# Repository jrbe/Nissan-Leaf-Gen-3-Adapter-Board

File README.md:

# Nissan-Leaf-Gen-3-Adapter-Board
This is an Open Inverter Mini Mainboard adapter PC board for a Gen. 3 Nissan Leaf inverter. This gives a user full control over the inverter for DIY EV projects. Designed in Kicad 7.

This is a work in progress, V0.0.4 is current but is not a production release yet.  Johu (Open Inverter) could not get a motor spinning in closed loop control. There are also many board settings to work out still.

The Wiki for this board is here, https://openinverter.org/wiki/Nissan_Leaf_Gen_3_(2018_up_EM57)

There are many options built into this board. Multi-footprints for the 2 main connectors for SMD and through hole options, E-stop bypass or use, auxiliary outputs with different voltages, etc. See the wiki above for details.

If you have questions please check the Wiki first.  If your question is not answered there please post questions, comments, ideas, etc. in this thread, [https://openinverter.org/forum/viewtopic.php?t=4565](https://openinverter.org/forum/viewtopic.php?t=4565)

The original development thread is here, https://openinverter.org/forum/viewtopic.php?t=2324  Please do not post questions here.

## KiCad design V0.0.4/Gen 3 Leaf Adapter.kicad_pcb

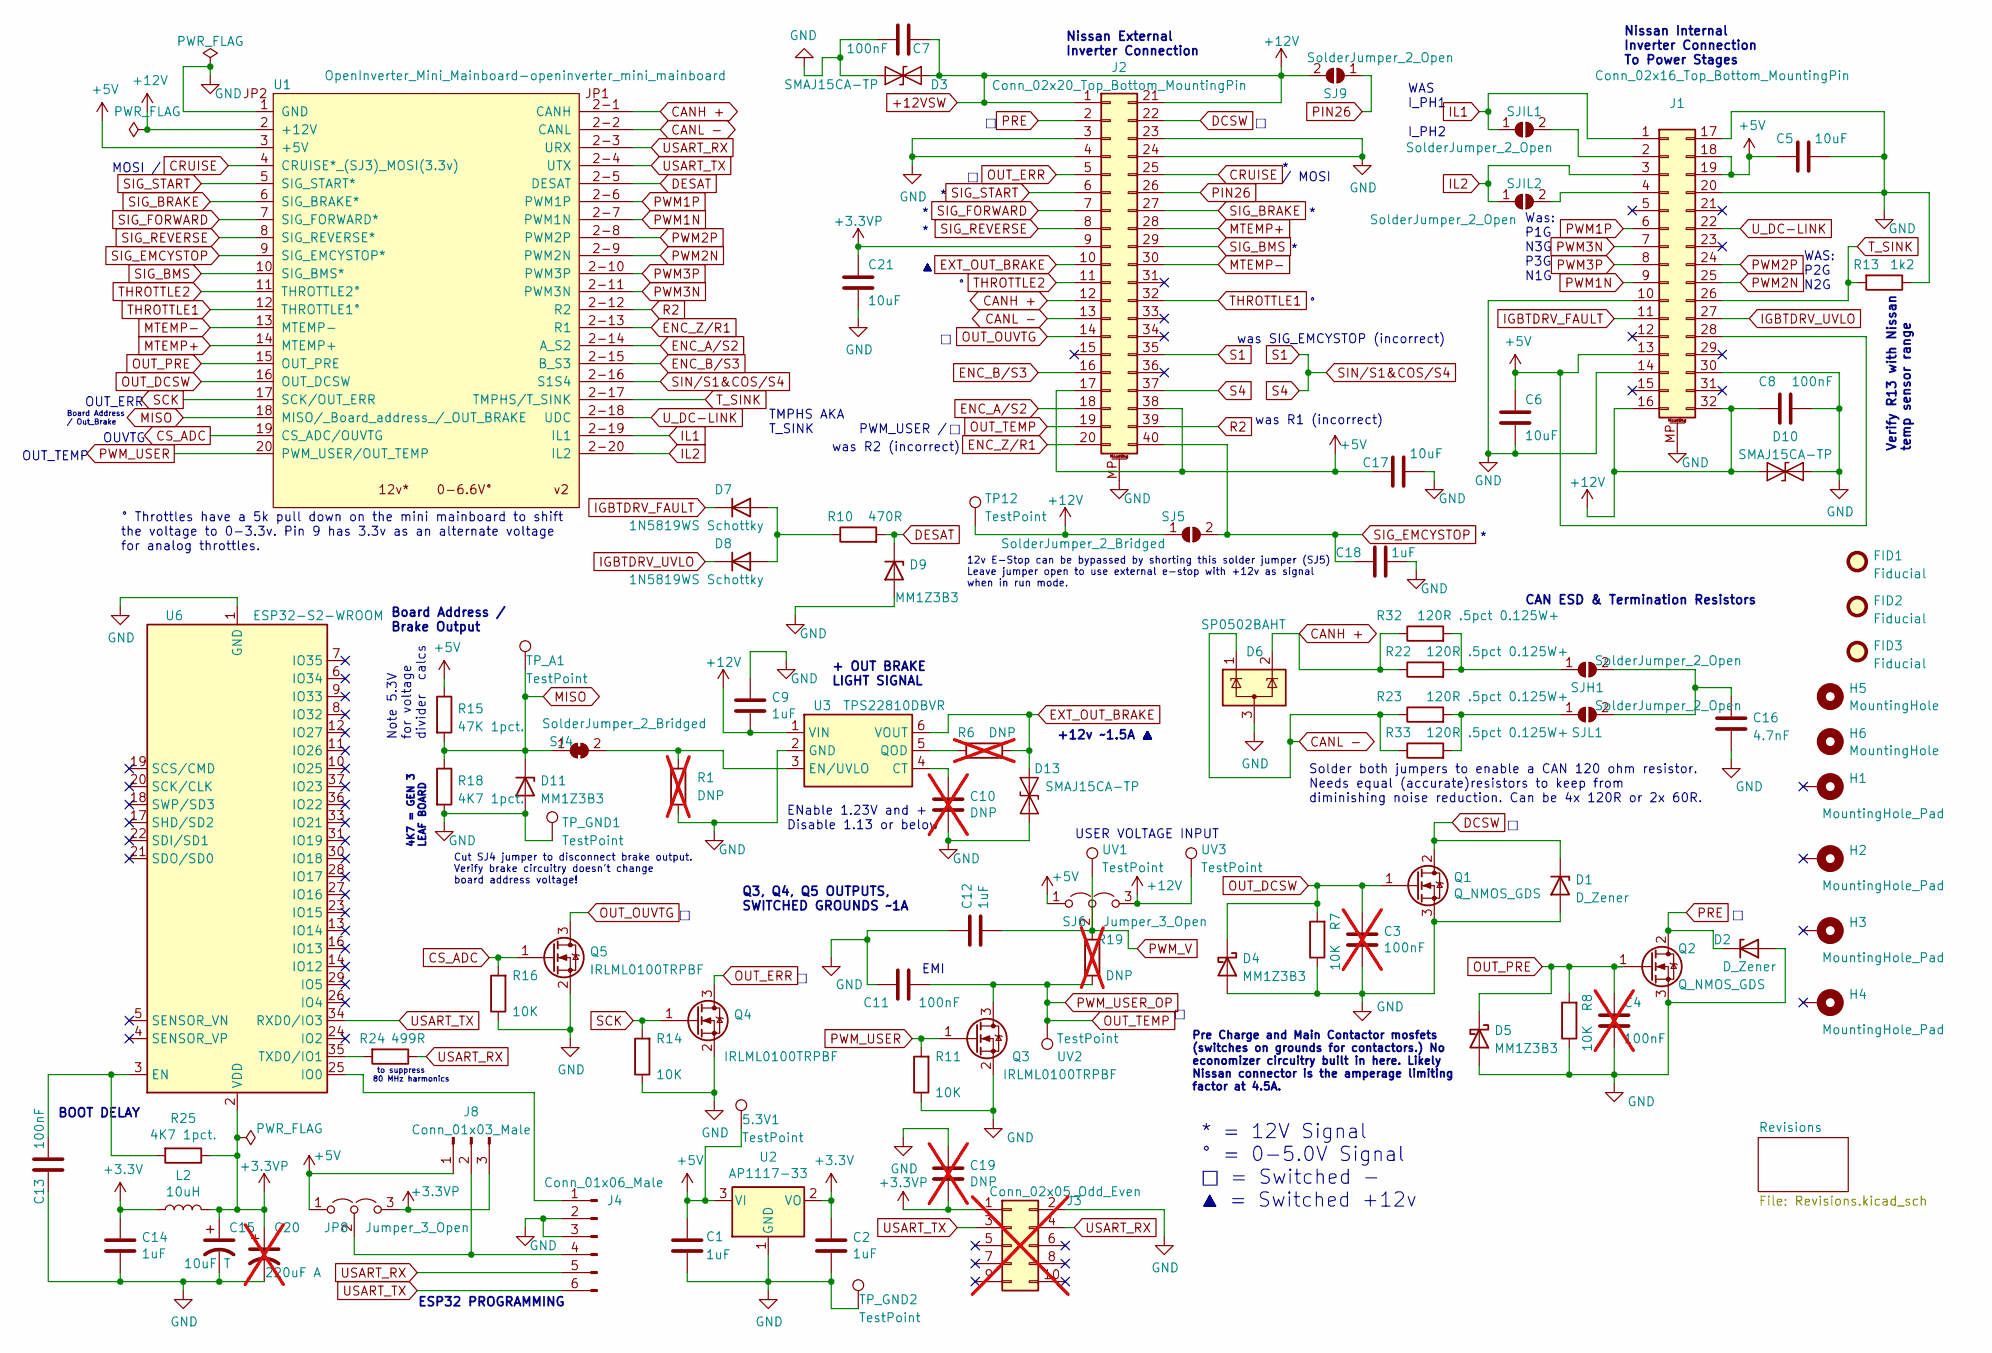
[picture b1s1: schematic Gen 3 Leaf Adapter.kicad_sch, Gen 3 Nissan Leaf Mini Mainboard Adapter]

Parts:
5.3V1: TestPoint; TestPoint_THTPad_D2.0mm_Drill1.0mm
C1, C2, C9, C12, C14, C18: 1uF; C_0805_2012Metric_Pad1.18x1.45mm_HandSolder; MFG Part # CL21B105KBFNNNE; LCSC Part C28323
C3, C4: 100nF; C_0805_2012Metric_Pad1.18x1.45mm_HandSolder; MFG Part # CL21B104KCFNNNE; LCSC Part C28233; not fitted
C5, C6, C17, C21: 10uF; C_0805_2012Metric_Pad1.18x1.45mm_HandSolder; MFG Part # CL21A106KAYNNNE; LCSC Part C15850
C7, C8, C11, C13: 100nF; C_0805_2012Metric_Pad1.18x1.45mm_HandSolder; MFG Part # CL21B104KCFNNNE; LCSC Part C28233
C10: DNP; C_0805_2012Metric_Pad1.18x1.45mm_HandSolder; LCSC Part DNP; not fitted
C15: 10uF T; CP_EIA-3216-18_Kemet-A_Pad1.58x1.35mm_HandSolder; MFG Part # TAJA106K016RNJ; LCSC Part C7171
C16: 4.7nF; C_0805_2012Metric_Pad1.18x1.45mm_HandSolder; MFG Part # 0805B472K500NT; LCSC Part C1744
C19: DNP; C_0805_2012Metric_Pad1.18x1.45mm_HandSolder; not fitted
C20: 220uF A; CP_Elec_10x10.5; not fitted
D1, D2: D_Zener; D_SMB_Handsoldering; LCSC Part C1972924
D3, D10, D13: SMAJ15CA-TP; D_SMA; MFG Part # SMAJ15CA-TP; LCSC Part C129543
D4, D5, D9, D11: MM1Z3B3; D_SOD-123; MFG Part # MM1Z3B3; LCSC Part C108453
D6: SP0502BAHT; SOT-23; MFG Part # PESD1CAN; LCSC Part C907838
D7, D8: 1N5819WS Schottky; D_SOD-323; MFG Part # 1N5819WS; LCSC Part C191023
FID1, FID2, FID3: Fiducial; Fiducial_1mm_Mask2mm
H1, H2, H3, H4: MountingHole_Pad; MountingHole_4.3mm_M4_Pad_Via
H5, H6: MountingHole; MountingHole_4.3mm_M4
J1: Conn_02x16_Top_Bottom_MountingPin; 32 Pin Internal Nissan Inverter Connector Merged Footprints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; LCSC Part DNP
J2: Conn_02x20_Top_Bottom_MountingPin; TE_1318384-2_Dual_FP; LCSC Part DNP
J3: Conn_02x05_Odd_Even; PinHeader_2x05_P2.54mm_Horizontal; LCSC Part DNP; not fitted
J4: Conn_01x06_Male; PinHeader_1x06_P2.54mm_Vertical; LCSC Part DNP
J8: Conn_01x03_Male; PinHeader_1x03_P2.54mm_Vertical; LCSC Part DNP
JP8: Jumper_3_Open; SolderJumper-3_P1.3mm_Open_RoundedPad1.0x1.5mm
L2: 10uH; Inductor_Sunlord_4030; MFG Part # SWPA4030S100MT; LCSC Part C38117
Q1, Q2: Q_NMOS_GDS; TO-252-2; MFG Part # IRLR3410TRPBF; LCSC Part C3017
Q3, Q4, Q5: IRLML0100TRPBF; SOT-23; MFG Part # IRLML0100TRPBF; LCSC Part C53658
R1: DNP; R_0805_2012Metric_Pad1.20x1.40mm_HandSolder; not fitted
R6, R19: DNP; R_0805_2012Metric_Pad1.20x1.40mm_HandSolder; LCSC Part DNP; not fitted
R7, R8, R11, R14, R16: 10K; R_0805_2012Metric_Pad1.20x1.40mm_HandSolder; MFG Part # 0805W8F1002T5E; LCSC Part C17414
R10: 470R; R_0805_2012Metric_Pad1.20x1.40mm_HandSolder; MFG Part # 0805W8F4700T5E; LCSC Part C17710
R13: 1k2; R_0805_2012Metric_Pad1.20x1.40mm_HandSolder; MFG Part # 0805W8F1201T5E; LCSC Part C17379
R15: 47K 1pct.; R_0805_2012Metric_Pad1.20x1.40mm_HandSolder; MFG Part # 0805W8F4702T5E; LCSC Part C17713
R18, R25: 4K7 1pct.; R_0805_2012Metric_Pad1.20x1.40mm_HandSolder; MFG Part # 0805W8F4701T5E; LCSC Part C17673
R22, R23, R32, R33: 120R .5pct 0.125W+; R_1206_3216Metric_Pad1.30x1.75mm_HandSolder; LCSC Part C2984524
R24: 499R; R_0805_2012Metric_Pad1.20x1.40mm_HandSolder; MFG Part # 0805W8F4990T5E; LCSC Part C17722
SJ4: SolderJumper_2_Bridged; SolderJumper-2_P1.3mm_Bridged_RoundedPad1.0x1.5mm
SJ5: SolderJumper_2_Bridged; SolderJumper-2_P1.3mm_Open_RoundedPad1.0x1.5mm
SJ6: Jumper_3_Open; SolderJumper-3_P1.3mm_Open_RoundedPad1.0x1.5mm
SJ9: SolderJumper_2_Open; SolderJumper-2_P1.3mm_Open_RoundedPad1.0x1.5mm
SJH1: SolderJumper_2_Open; SolderJumper-2_P1.3mm_Open_RoundedPad1.0x1.5mm
SJIL1, SJIL2: SolderJumper_2_Open; SolderJumper-2_P1.3mm_Open_RoundedPad1.0x1.5mm
SJL1: SolderJumper_2_Open; SolderJumper-2_P1.3mm_Open_RoundedPad1.0x1.5mm
TP12: TestPoint; TestPoint_THTPad_D2.0mm_Drill1.0mm
TP_A1: TestPoint; TestPoint_THTPad_D2.0mm_Drill1.0mm
TP_GND1, TP_GND2: TestPoint; TestPoint_THTPad_D2.0mm_Drill1.0mm
U1: OpenInverter_Mini_Mainboard-openinverter_mini_mai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; OPENINVERTER_MINI_MAINBOARD
U2: AP1117-33; SOT-223-3_TabPin2; MFG Part # AMS1117-3.3; LCSC Part C6186
U3: TPS22810DBVR; SOT-23-6_Handsoldering; MFG Part # TPS22810DBVR; LCSC Part C205990
U6: ESP32-S2-WROOM; ESP32-WROOM-32; MFG Part # ESP32-WROOM-32-N4; LCSC Part C82899
UV1, UV2, UV3: TestPoint; TestPoint_THTPad_D2.0mm_Drill1.0mm

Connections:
+3.3VP: C15.1, C19.2, C20.1, C21.1, J2.9, J3.1, J8.3, JP8.3 (B), L2.2, R25.1, U6.2 (VDD)
+3V3: C2.1, C14.1, L2.1, U2.2 (VO)
+5V: 5.3V1.1, C1.1, C5.1, C6.1, C17.1, J1.13, J1.18, J1.19, J1.28, J2.17, J2.38, J8.1, JP8.1 (A), R15.1, SJ6.1 (A), U1.3 (+5V), U2.3 (VI)
+12VSW: C7.1, C8.1, C9.2, D3.2 (A2), D10.2 (A2), J1.16, J1.32, J2.1, J2.21, SJ5.1 (A), SJ6.3 (B), SJ9.2 (B), TP12.1, U1.2 (+12V), U3.1 (VIN), UV3.1
CANH +: D6.2 (K), J2.12, R22.1, R32.1, U1.2-1 (CANH)
CANL -: D6.1 (K), J2.13, R23.1, R33.1, U1.2-2 (CANL)
CRUISE: J2.25, U1.4 (CRUISE*_(SJ3)_MOSI(3.3v))
CS_ADC: Q5.1 (G), R16.2, U1.19 (CS_ADC/OUVTG)
DCSW: D1.1 (K), J2.22, Q1.2 (D)
DESAT: D9.1 (K), R10.2, U1.2-5 (DESAT)
ENC_A/S2: J2.18, U1.2-14 (A_S2)
ENC_B/S3: J2.16, U1.2-15 (B_S3)
ENC_Z/R1: J2.20, U1.2-13 (R1)
EXT_OUT_BRAKE: D13.1 (A1), J2.10, R6.1, U3.6 (VOUT)
GND: C1.2, C2.2, C3.2, C4.2, C5.2, C6.2, C7.2, C8.2, C9.1, C10.2, C11.2, C12.1, C13.1, C14.2, C15.2, C16.2, C17.2, C18.2, C19.1, C20.2, C21.2, D1.2 (A), D2.2 (A), D3.1 (A1), D4.2 (A), D5.2 (A), D6.3 (A), D9.2 (A), D10.1 (A1), D11.2 (A), D13.2 (A2), J1.10, J1.14, J1.17, J1.20, J1.30, J1.MP (MountPin), J2.3, J2.4, J2.23, J2.24, J2.MP (MountPin), J3.2, J4.2, J4.3, Q1.3 (S), Q2.3 (S), Q3.2 (S), Q4.2 (S), Q5.2 (S), R1.2, R7.1, R8.1, R11.1, R13.1, R14.1, R16.1, R18.2, TP_GND1.1, TP_GND2.1, U1.1 (GND), U2.1 (GND), U3.2 (GND), U6.1 (GND), U6.15 (GND), U6.38 (GND), U6.39 (GND); also elsewhere on the board
IGBTDRV_FAULT: D7.1 (K), J1.11
IGBTDRV_UVLO: D8.1 (K), J1.27
IL1: J1.1, SJIL1.1 (A), U1.2-19 (IL1)
IL2: J1.3, SJIL2.1 (A), U1.2-20 (IL2)
MISO: D11.1 (K), R15.2, R18.1, SJ4.1 (A), TP_A1.1, U1.18 (MISO/_Board_address_/_OUT_BRAKE)
MTEMP+: J2.28, U1.14 (MTEMP+)
MTEMP-: J2.30, U1.13 (MTEMP-)
unnamed: D7.2 (A), D8.2 (A), R10.1
unnamed: J1.2, SJIL1.2 (B)
unnamed: J1.4, SJIL2.2 (B)
unnamed: J4.1, U6.25 (IO0)
unnamed: J4.4, J8.2, JP8.2 (C)
unnamed: R1.1, SJ4.2 (B), U3.3 (EN/UVLO)
unnamed: R22.2, R32.2, SJH1.1 (A)
unnamed: C16.1, SJH1.2 (B), SJL1.2 (B)
unnamed: R23.2, R33.2, SJL1.1 (A)
unnamed: C10.1, U3.4 (CT)
unnamed: R6.2, U3.5 (QOD)
unnamed: C13.2, R25.2, U6.3 (EN)
unnamed: R24.2, U6.35 (TXD0/IO1)
OUT_DCSW: C3.1, D4.1 (K), Q1.1 (G), R7.2, U1.16 (OUT_DCSW)
OUT_ERR: J2.5, Q4.3 (D)
OUT_OUVTG: J2.14, Q5.3 (D)
OUT_PRE: C4.1, D5.1 (K), Q2.1 (G), R8.2, U1.15 (OUT_PRE)
OUT_TEMP: C11.1, J2.19, Q3.3 (D), R19.1, UV2.1
PIN26: J2.26, SJ9.1 (A)
PRE: D2.1 (K), J2.2, Q2.2 (D)
PWM1N: J1.9, U1.2-7 (PWM1N)
PWM1P: J1.6, U1.2-6 (PWM1P)
PWM2N: J1.25, U1.2-9 (PWM2N)
PWM2P: J1.24, U1.2-8 (PWM2P)
PWM3N: J1.7, U1.2-11 (PWM3N)
PWM3P: J1.8, U1.2-10 (PWM3P)
PWM_USER: Q3.1 (G), R11.2, U1.20 (PWM_USER/OUT_TEMP)
PWM_V: C12.2, R19.2, SJ6.2 (C), UV1.1
R2: J2.39, U1.2-12 (R2)
S1: J2.35, J2.37, U1.2-16 (S1S4)
SCK: Q4.1 (G), R14.2, U1.17 (SCK/OUT_ERR)
SIG_BMS: J2.29, U1.10 (SIG_BMS*)
SIG_BRAKE: J2.27, U1.6 (SIG_BRAKE*)
SIG_EMCYSTOP: C18.1, J2.40, SJ5.2 (B), U1.9 (SIG_EMCYSTOP*)
SIG_FORWARD: J2.7, U1.7 (SIG_FORWARD*)
SIG_REVERSE: J2.8, U1.8 (SIG_REVERSE*)
SIG_START: J2.6, U1.5 (SIG_START*)
THROTTLE1: J2.32, U1.12 (THROTTLE1°)
THROTTLE2: J2.11, U1.11 (THROTTLE2°)
T_SINK: J1.26, R13.2, U1.2-17 (TMPHS/T_SINK)
USART_RX: J3.4, J4.5, R24.1, U1.2-3 (URX)
USART_TX: J3.3, J4.6, U1.2-4 (UTX), U6.34 (RXD0/IO3)
U_DC-LINK: J1.22, U1.2-18 (UDC)

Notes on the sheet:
PWM_USER /
4K7 = GEN 3 LEAF BOARD
OUT_ERR
/ MOSI
+ OUT BRAKE LIGHT SIGNAL
Was: P1G N3G P3G N1G
BOOT DELAY
TMPHS AKA T_SINK
MOSI /
* = 12V Signal ° = 0-5.0V Signal □ = Switched - ▲ = Switched +12v
EMI
Solder both jumpers to enable a CAN 120 ohm resistor. Needs equal (accurate)resistors to keep from diminishing noise reduction. Can be 4x 120R or 2x 60R.
CAN ESD & Termination Resistors
Board Address / Out_Brake
Nissan Internal Inverter Connection To Power Stages
was R2 (incorrect)
ESP32 PROGRAMMING
Board Address / Brake Output
was R1 (incorrect)
WAS I_PH1 I_PH2
+12v ~1.5A ▲
12v E-Stop can be bypassed by shorting this solder jumper (SJ5) Leave jumper open to use external e-stop with +12v as signal when in run mode.
° Throttles have a 5k pull down on the mini mainboard to shift the voltage to 0-3.3v. Pin 9 has 3.3v as an alternate voltage for analog throttles.
Nissan External Inverter Connection
USER VOLTAGE INPUT
Pre Charge and Main Contactor mosfets (switches on grounds for contactors.) No economizer circuitry built in here. Likely Nissan connector is the amperage limiting factor at 4.5A.
Note 5.3V for voltage divider calcs
Verify R13 with Nissan temp sensor range
OUVTG
was SIG_EMCYSTOP (incorrect)
Cut SJ4 jumper to disconnect brake output. Verify brake circuitry doesn't change board address voltage!
WAS: P2G N2G
ENable 1.23V and + Disable 1.13 or below
to suppress 80 MHz harmonics
OUT_TEMP
Q3, Q4, Q5 OUTPUTS, SWITCHED GROUNDS ~1A

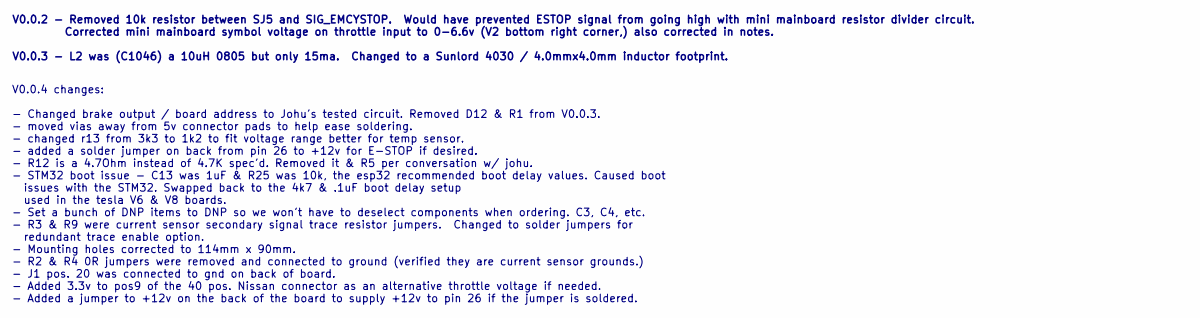
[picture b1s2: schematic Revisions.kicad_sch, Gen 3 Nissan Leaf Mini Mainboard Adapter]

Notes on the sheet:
V0.0.2 - Removed 10k resistor between SJ5 and SIG_EMCYSTOP. Would have prevented ESTOP signal from going high with mini mainboard resistor divider circuit. Corrected mini mainboard symbol voltage on throttle input to 0-6.6v (V2 bottom right corner,) also corrected in notes. V0.0.3 - L2 was (C1046) 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
V0.0.4 changes: - Changed brake output / board address to Johu's tested circuit. Removed D12 & R1 from V0.0.3. - moved vias away from 5v connector pads to help ease soldering. - changed r13 from 3k3 to 1k2 to fit voltage range better for temp sensor. - added a solder jumper on back from pin 26 to +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

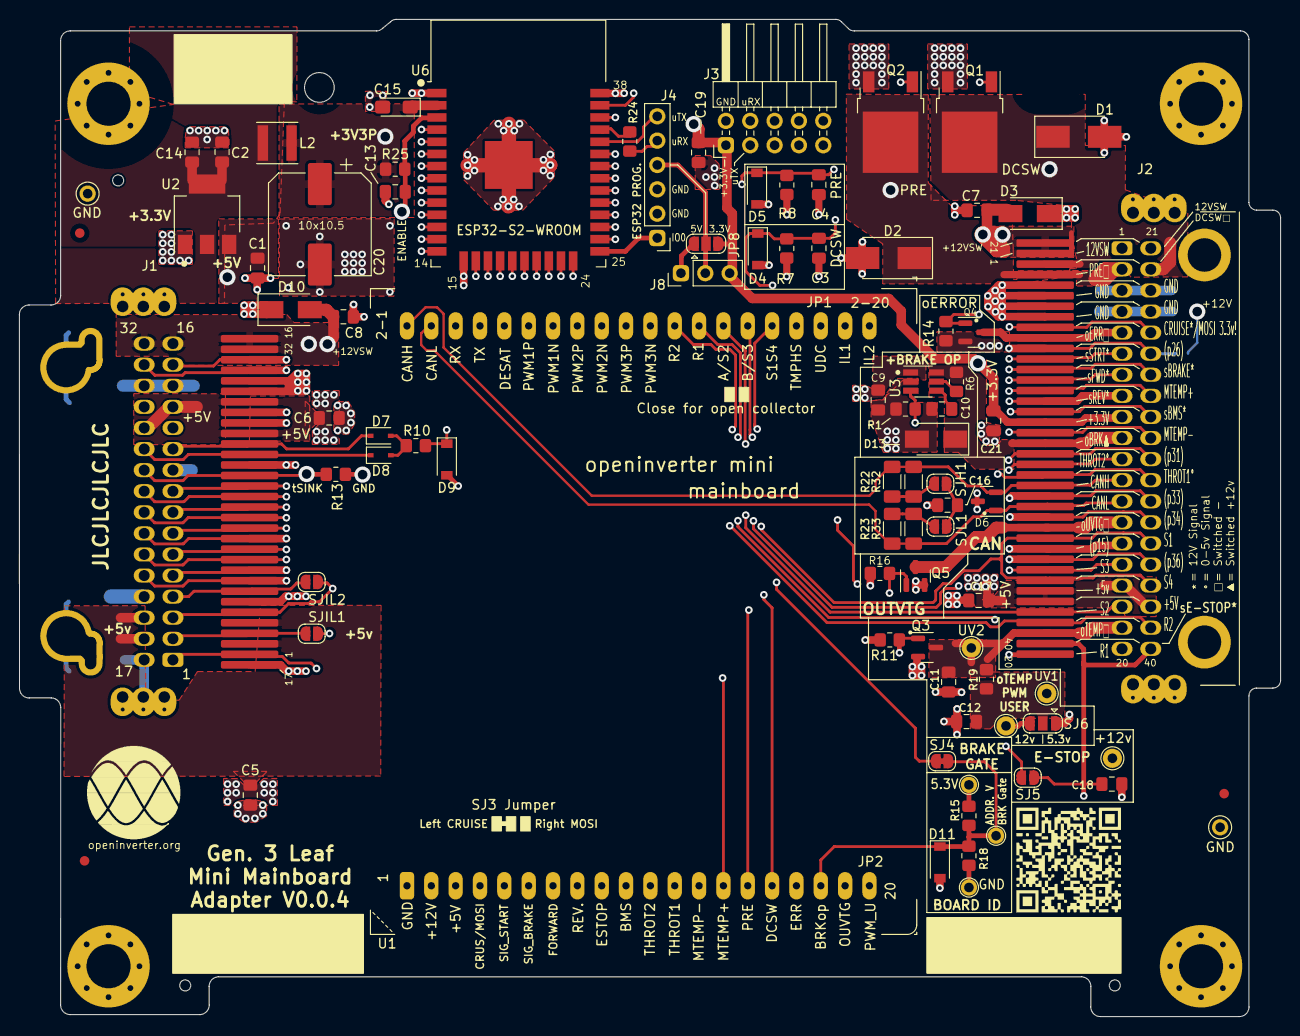
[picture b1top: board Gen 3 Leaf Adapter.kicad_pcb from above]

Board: 4 copper layers, 131.6 x 104.0 mm, 94 parts (1 on the bottom side), 65 nets.

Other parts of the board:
TP_GND1#2: TestPoint; TestPoint_THTPad_D2.0mm_Drill1.0mm
U$2: OI_LOGO

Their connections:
GND: TP_GND1#2.1; also elsewhere on the board

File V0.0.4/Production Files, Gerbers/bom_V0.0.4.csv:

Designator,Footprint,Quantity,Value,LCSC Part #
"5.3V1, TP12, TP_A1, TP_GND1_2, TP_GND1, TP_GND2, UV1, UV2, UV3",TestPoint_THTPad_D2.0mm_Drill1.0mm,9,TestPoint,-
"C1, C12, C14, C18, C2, C9",0805,6,1uF,C28323
"C11, C13, C7, C8",0805,4,100nF,C28233
C15,CP_EIA-3216-18_Kemet-A_Pad1.58x1.35mm_HandSolder,1,10uF T,C7171
C16,0805,1,4.7nF,C1744
"C17, C21, C5, C6",0805,4,10uF,C15850
"D1, D2",D_SMB_Handsoldering,2,D_Zener,C1972924
"D10, D13, D3",D_SMA,3,SMAJ15CA-TP,C129543
"D11, D4, D5, D9",D_SOD-123,4,MM1Z3B3,C108453
D6,SOT-23,1,SP0502BAHT,C907838
"D7, D8",D_SOD-323,2,1N5819WS Schottky,C191023
"H1, H2, H3, H4",MountingHole_4.3mm_M4_Pad_Via,4,MountingHole_Pad,-
"H5, H6",MountingHole_4.3mm_M4,2,MountingHole,-
J4,PinHeader_1x06_P2.54mm_Vertical,1,Conn_01x06_Male,DNP
J8,PinHeader_1x03_P2.54mm_Vertical,1,Conn_01x03_Male,DNP
"JP8, SJ6",SolderJumper-3_P1.3mm_Open_RoundedPad1.0x1.5mm,2,Jumper_3_Open,-
L2,Inductor_Sunlord_4030,1,10uH,C38117
"Q1, Q2",TO-252-2,2,Q_NMOS_GDS,C3017
"Q3, Q4, Q5",SOT-23,3,IRLML0100TRPBF,C53658
R10,0805,1,470R,C17710
"R11, R14, R16, R7, R8",0805,5,10K,C17414
R13,0805,1,1k2,C17379
R15,0805,1,47K 1pct.,C17713
"R18, R25",0805,2,4K7 1pct.,C17673
"R22, R23, R32, R33",1206,4,120R  .5pct  0.125W+,C2984524
R24,0805,1,499R,C17722
SJ4,SolderJumper-2_P1.3mm_Bridged_RoundedPad1.0x1.5mm,1,SolderJumper_2_Bridged,-
SJ5,SolderJumper-2_P1.3mm_Open_RoundedPad1.0x1.5mm,1,SolderJumper_2_Bridged,-
"SJ9, SJH1, SJIL1, SJIL2, SJL1",SolderJumper-2_P1.3mm_Open_RoundedPad1.0x1.5mm,5,SolderJumper_2_Open,-
U1,OPENINVERTER_MINI_MAINBOARD,1,OpenInverter_Mini_Mainboard-openinverter_mini_mainboard,-
U2,SOT-223-3_TabPin2,1,AP1117-33,C6186
U3,SOT-23-6_Handsoldering,1,TPS22810DBVR,C205990
U6,ESP32-WROOM-32,1,ESP32-S2-WROOM,C82899

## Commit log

2023-10-23 Upload of V0.0.1
    Uploaded the adapter board pcb files done in Kicad 6. This is for 3rd gen (aka gen 3) Nissan Leaf inverters to adapt to using the Open Inverter Mini Mainboard.
2023-10-24 V0.0.2
    Removed R17, corrected throttle voltages from 0-3.3 to 0-6.6v, corrected schematic notes, mini mainboard symbol (V2), updated silkscreen to V0.0.2, and added a 2nd page to the schematic to track revi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
2023-11-15 V0.0.3 update
    Corrected L2 inductor to one properly sized. From 0805 to a Sunlord 4030 / 4.0mmX4.0mm inductor.
2023-11-15 V0.0.3 update
    Corrected L2 to a sunlord 4030 / 4x4mm inductor.
2023-11-15 V0.0.3
2024-02-19 Update README.md
    Notify about V0.0.4 wip
2024-04-03 Create Archive
2024-04-03 V0.0.4 Upload
    Uploaded V0.0.4. Archived V0.0.3.
2024-04-03 Moved Readme
    Moved Readme
2024-04-10 Added board images
    Added board & layer images
2024-04-11 Added missing Kicad files, tried to correct folder structure to match errors.
    Added missing Kicad files, tried to correct folder structure to match errors.
2024-04-11 Added more missing files
    Added more missing files
